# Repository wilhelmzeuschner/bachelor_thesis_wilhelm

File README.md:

# Bachelor Thesis Wilhelm Zeuschner
This repo contains select files of my bachelor thesis

More details can be found on my website where I wrote an article about my thesis.

www.wizeus.de/lmm-ba

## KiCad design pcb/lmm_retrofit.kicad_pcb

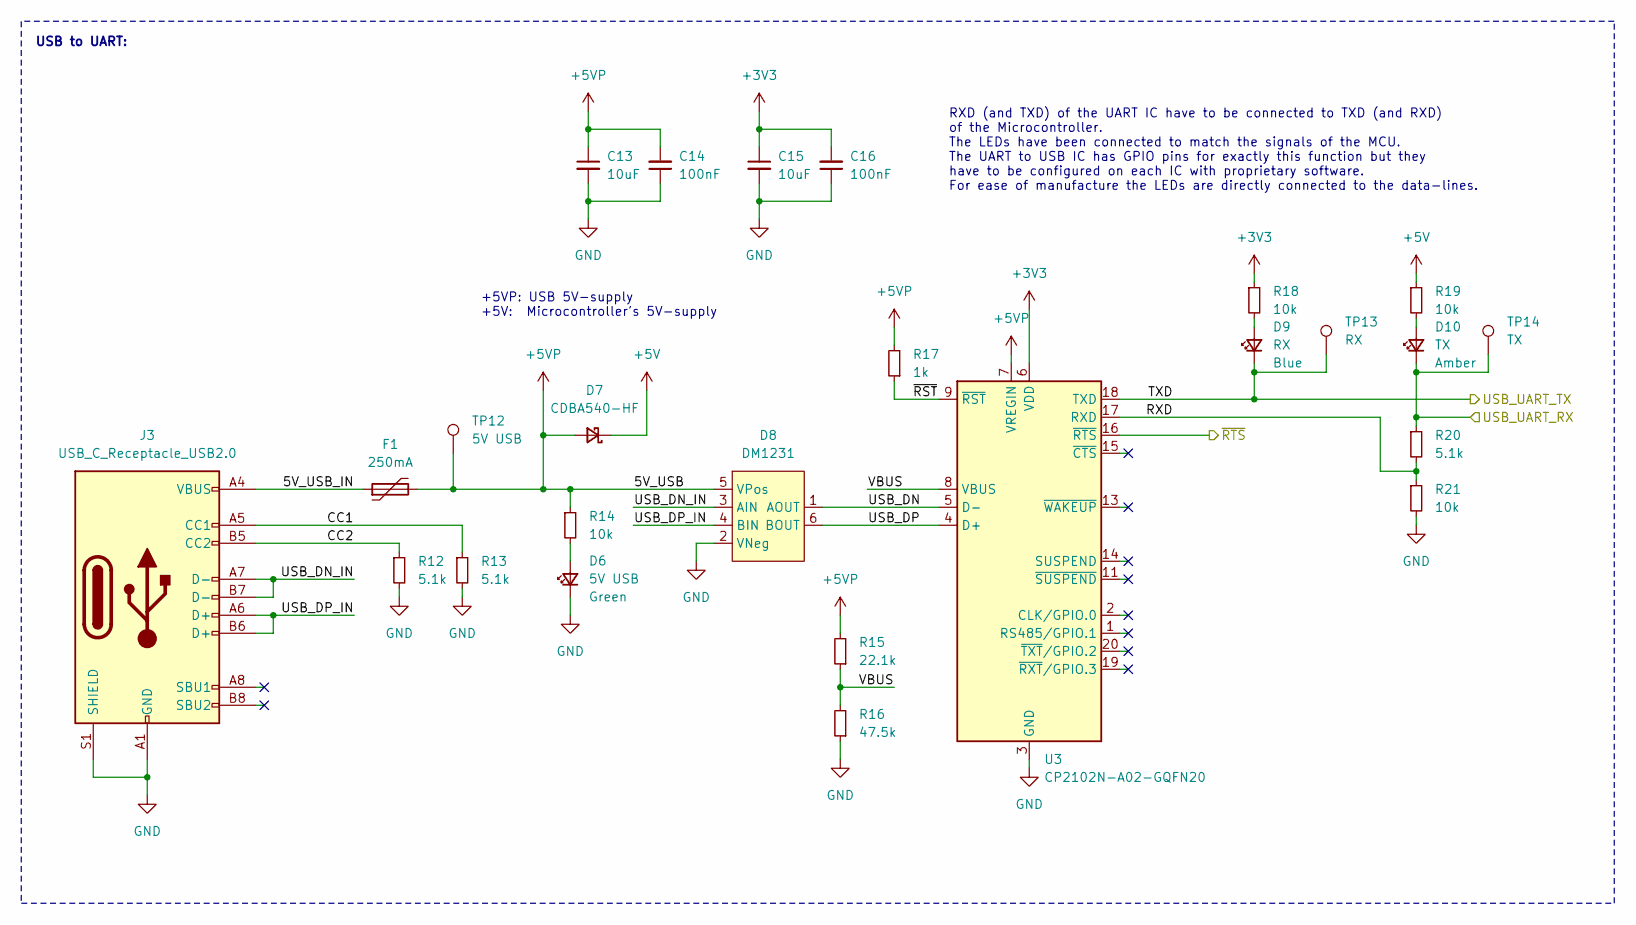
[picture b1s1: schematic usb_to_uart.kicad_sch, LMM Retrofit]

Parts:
C13, C15: 10uF; C_0805_2012Metric; MPN TMK212BBJ106MGHT; Digi-Key Part Number 587-6440-1-ND
C14, C16: 100nF; C_0805_2012Metric; MPN UMK212B7104KGHT; Digi-Key Part Number 587-3508-1-ND
D6: 5V USB; LED_0805_2012Metric_Silkscreen_Text; MPN 150080GS75000; Digi-Key Part Number 732-4983-1-ND
D7: CDBA540-HF; D_SMA; MPN CDBA540-HF; Digi-Key Part Number 641-1707-1-ND
D8: DM1231; SOT-23-6; MPN DM1231-02SO-7; Digi-Key Part Number DM1231-02SO-7DICT-ND
D9: RX; LED_0805_2012Metric_Silkscreen_Text; MPN 150080BS75000; Digi-Key Part Number 732-4982-1-ND
D10: TX; LED_0805_2012Metric_Silkscreen_Text; MPN 150080AS75000; Digi-Key Part Number 732-150080AS75000CT-ND
F1: 250mA; Fuse_1206_3216Metric; MPN 0ZCJ0025AF2E; Digi-Key Part Number 507-1799-1-ND
J3: USB_C_Receptacle_USB2.0; USB_C_Receptacle_GCT_USB4105-GF-A; MPN USB4105-GF-A; Digi-Key Part Number 2073-USB4105-GF-ACT-ND
R12, R13, R20: 5.1k; R_0805_2012Metric; MPN CRG0805F5K1; Digi-Key Part Number A126379CT-ND
R14, R18, R19, R21: 10k; R_0805_2012Metric; MPN CRGCQ0805J10K; Digi-Key Part Number A130140CT-ND
R15: 22.1k; R_0805_2012Metric; MPN CR0805-FX-2212ELF; Digi-Key Part Number CR0805-FX-2212ELFCT-ND
R16: 47.5k; R_0805_2012Metric; MPN CR0805-FX-4752ELF; Digi-Key Part Number 118-CR0805-FX-4752ELFCT-ND
R17: 1k; R_0805_2012Metric; MPN CRGCQ0805F1K0; Digi-Key Part Number A129749CT-ND
TP12: 5V USB; TestPoint_Pad_D1.0mm_Text_Silkscreen
TP13: RX; TestPoint_Pad_D1.0mm_Text_Silkscreen
TP14: TX; TestPoint_Pad_D1.0mm_Text_Silkscreen
U3: CP2102N-A02-GQFN20; SiliconLabs_QFN-20-1EP_3x3mm_P0.5mm_EP1.8x1.8mm_Center_Via; MPN CP2102N-A02-GQFN20; Digi-Key Part Number 336-5885-ND

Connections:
+3V3: C15.1, C16.2, R18.1, U3.6 (VDD)
+5V: D7.1 (K), R19.1; also elsewhere on the board
+5VP: C13.1, C14.2, D7.2 (A), D8.5 (VPos), F1.2, R14.1, R15.2, R17.2, TP12.1, U3.7 (VREGIN)
/Microcontroller/D0/UART_RX: D9.1 (K), TP13.1, U3.18 (TXD); also elsewhere on the board
/Microcontroller/D1/UART_TX: D10.1 (K), R20.1, TP14.1; also elsewhere on the board
/Microcontroller/~DTR: U3.16 (~RTS); also elsewhere on the board
/USB to UART/5V_USB_IN: F1.1, J3.A4 (VBUS), J3.A9 (VBUS), J3.B4 (VBUS), J3.B9 (VBUS)
/USB to UART/CC1: J3.A5 (CC1), R13.1
/USB to UART/CC2: J3.B5 (CC2), R12.1
/USB to UART/RXD: R20.2, R21.1, U3.17 (RXD)
/USB to UART/USB_DN: D8.1 (AOUT), U3.5 (D-)
/USB to UART/USB_DN_IN: D8.3 (AIN), J3.A7 (D-), J3.B7 (D-)
/USB to UART/USB_DP: D8.6 (BOUT), U3.4 (D+)
/USB to UART/USB_DP_IN: D8.4 (BIN), J3.A6 (D+), J3.B6 (D+)
/USB to UART/VBUS: R15.1, R16.2, U3.8 (VBUS)
/USB to UART/~RST: R17.1, U3.9 (~RST)
unnamed: D6.2 (A), R14.2
unnamed: D9.2 (A), R18.2
unnamed: D10.2 (A), R19.2

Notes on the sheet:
+5VP: USB 5V-supply +5V: Microcontroller's 5V-supply
USB to UART:
RXD (and TXD) of the UART IC have to be connected to TXD (and RXD) of the Microcontroller. The LEDs have been connected to match the signals of the MCU. The UART to USB IC has GPIO pins for exactly this function but they have to be configured on each IC with proprietary software. For ease of manufa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

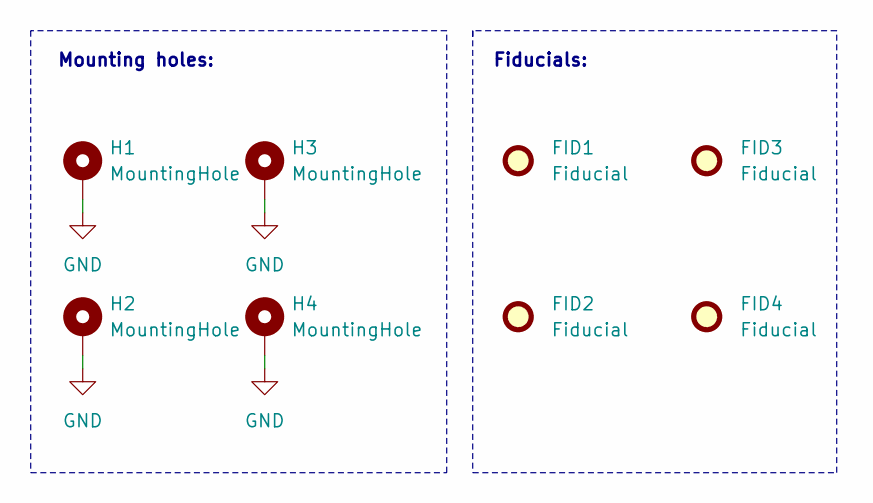
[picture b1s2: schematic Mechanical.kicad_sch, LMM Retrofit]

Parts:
FID1, FID2, FID3, FID4: Fiducial; Fiducial_0.5mm_Mask1mm
H1, H2, H3, H4: MountingHole; MountingHole_3.2mm_M3_Pad_Via

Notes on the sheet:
Fiducials:
Mounting holes:

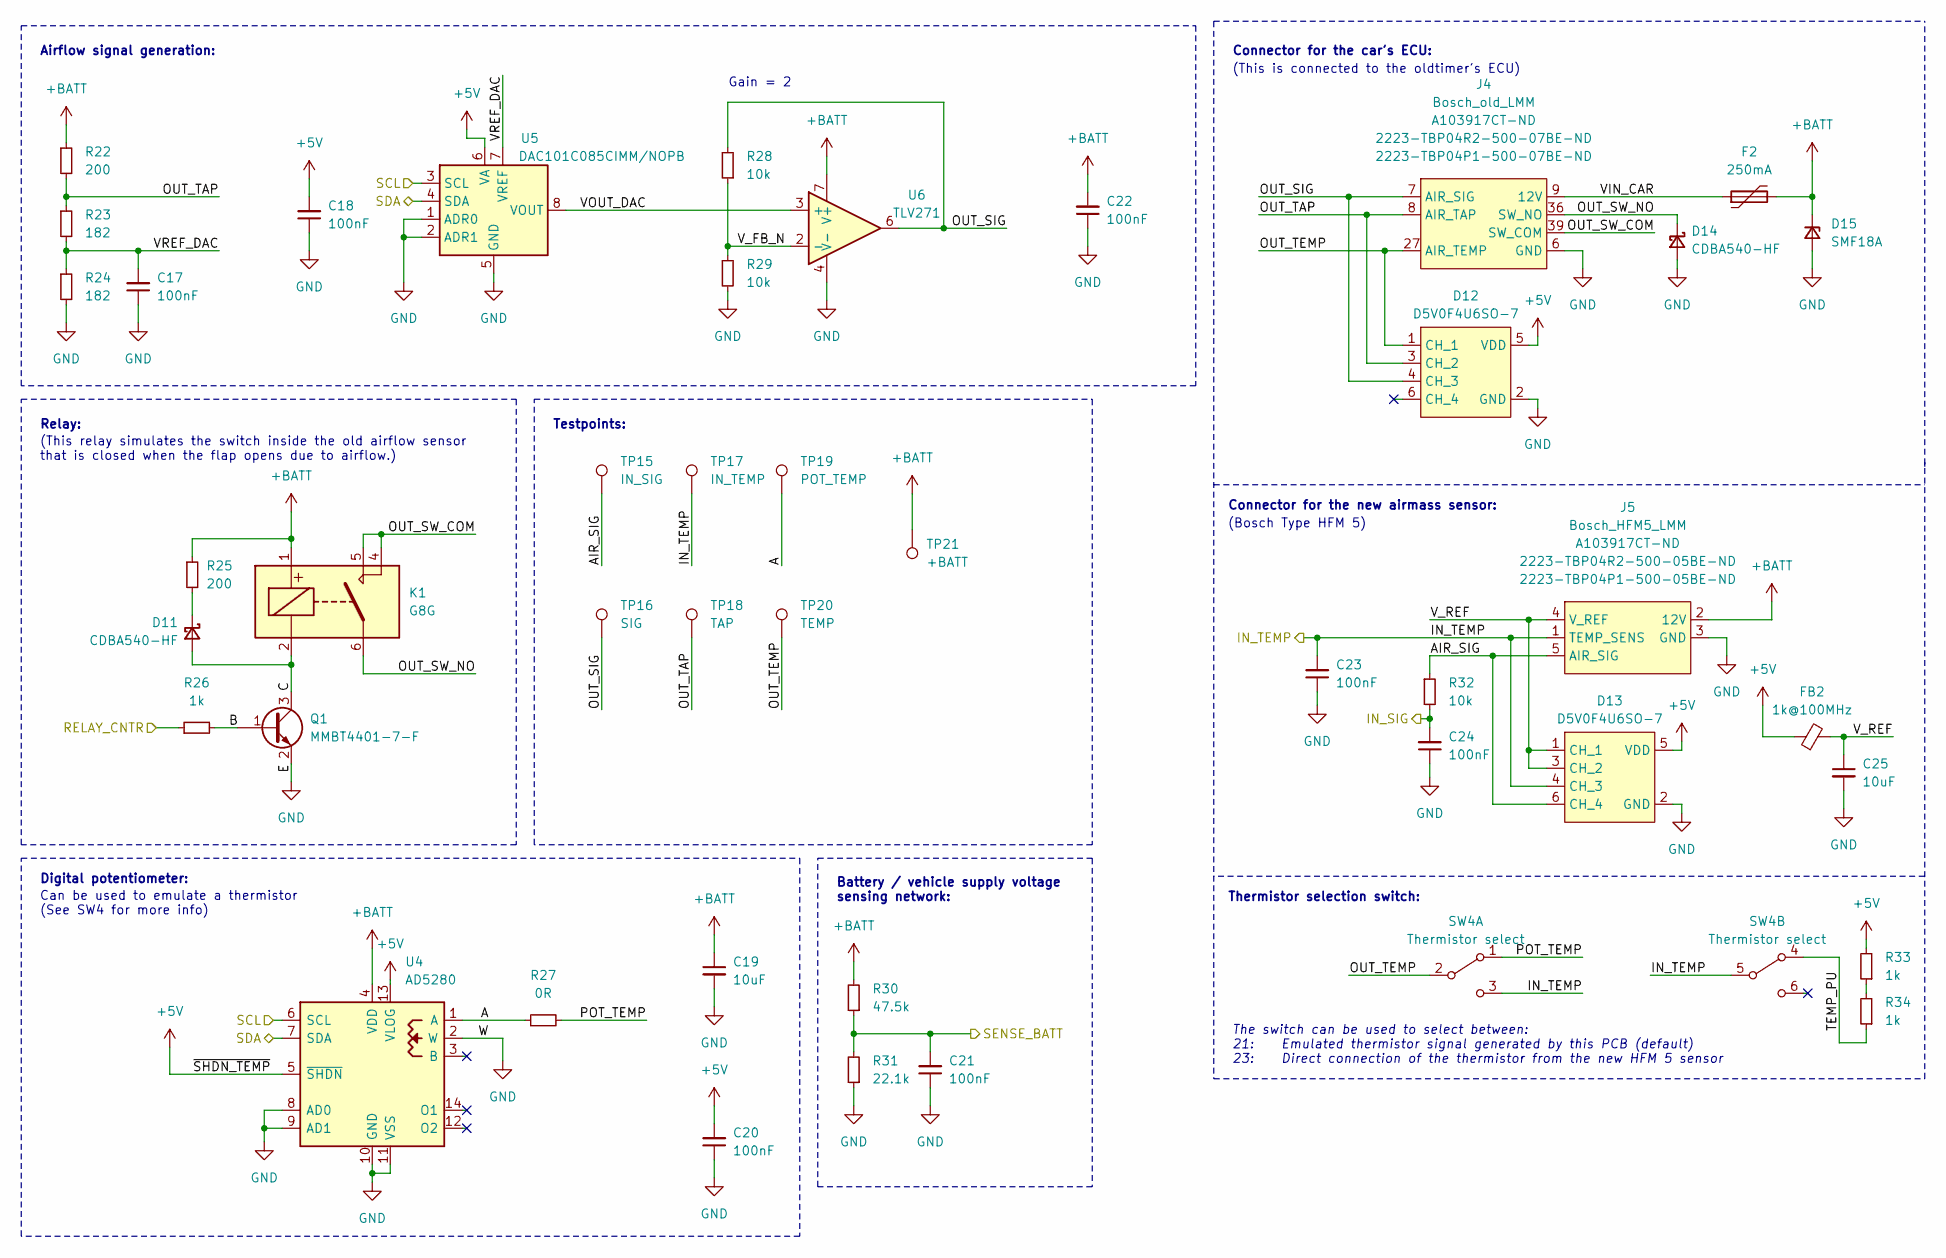
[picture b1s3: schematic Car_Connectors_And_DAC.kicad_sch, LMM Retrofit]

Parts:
C17, C18, C20, C21, C22, C23, C24: 100nF; C_0805_2012Metric; MPN UMK212B7104KGHT; Digi-Key Part Number 587-3508-1-ND
C19, C25: 10uF; C_0805_2012Metric; MPN TMK212BBJ106MGHT; Digi-Key Part Number 587-6440-1-ND
D11, D14: CDBA540-HF; D_SMA; MPN CDBA540-HF; Digi-Key Part Number 641-1707-1-ND
D12, D13: D5V0F4U6SO-7; SOT-23-6; MPN D5V0F4U6SO-7; Digi-Key Part Number D5V0F4U6SO-7DICT-ND
D15: SMF18A; D_SOD-123F; MPN SMF18A; Digi-Key Part Number F5820CT-ND
F2: 250mA; Fuse_1206_3216Metric; MPN 0ZCJ0025AF2E; Digi-Key Part Number 507-1799-1-ND
FB2: 1k@100MHz; L_0805_2012Metric; MPN ACML-0805-102-T; Digi-Key Part Number 535-ACML-0805-102-TCT-ND
J4: Bosch_old_LMM; Bosch_L_Jetronic_7-Pin_Male_Blade_Conn; MPN 0 280 203 002
J5: Bosch_HFM5_LMM; Bosch_Airmass_Senosor_5-Pin_Male_Blade_Connector; MPN 0 280 217 531
K1: G8G; G8G__SPST; MPN G8G-1A7R DC12 BY OMR1; Digi-Key Part Number 39-G8G-1A7RDC12BYOMR1-ND
Q1: MMBT4401-7-F; SOT-23; MPN MMBT4401-HF; Digi-Key Part Number 641-MMBT4401-HFCT-ND
R22, R25: 200; R_0805_2012Metric; MPN ESR10EZPF2000; Digi-Key Part Number RHM200AECT-ND
R23, R24: 182; R_0805_2012Metric; MPN CRCW0805182RFKEA; Digi-Key Part Number 541-182CCT-ND
R26, R33, R34: 1k; R_0805_2012Metric; MPN CRGCQ0805F1K0; Digi-Key Part Number A129749CT-ND
R27: 0R; R_0805_2012Metric; MPN AC0805JR-070RL; Digi-Key Part Number YAG3755CT-ND
R28, R29, R32: 10k; R_0805_2012Metric; MPN CRGCQ0805J10K; Digi-Key Part Number A130140CT-ND
R30: 47.5k; R_0805_2012Metric; MPN CR0805-FX-4752ELF; Digi-Key Part Number 118-CR0805-FX-4752ELFCT-ND
R31: 22.1k; R_0805_2012Metric; MPN CR0805-FX-2212ELF; Digi-Key Part Number CR0805-FX-2212ELFCT-ND
SW4: Thermistor select; JS202011SCQN; MPN JS202011SCQN; Digi-Key Part Number 401-2002-1-ND
TP15: IN_SIG; TestPoint_Pad_D1.0mm_Text_Silkscreen
TP16: SIG; TestPoint_Pad_D1.0mm_Text_Silkscreen
TP17: IN_TEMP; TestPoint_Pad_D1.0mm_Text_Silkscreen
TP18: TAP; TestPoint_Pad_D1.0mm_Text_Silkscreen
TP19: POT_TEMP; TestPoint_Pad_D1.0mm_Text_Silkscreen
TP20: TEMP; TestPoint_Pad_D1.0mm_Text_Silkscreen
TP21: +BATT; TestPoint_Pad_D1.0mm_Text_Silkscreen
U4: AD5280; TSSOP-14_4.4x5mm_P0.65mm; MPN AD5280BRUZ50; Digi-Key Part Number AD5280BRUZ50-ND
U5: DAC101C085CIMM/NOPB; VSSOP-8_3.0x3.0mm_P0.65mm; MPN DAC101C085CIMM/NOPB; Digi-Key Part Number DAC101C085CIMM/NOPBCT-ND
U6: TLV271; SOIC-8_3.9x4.9mm_P1.27mm; MPN TLV271QDRQ1; Digi-Key Part Number 296-38281-1-ND

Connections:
+5V: C18.2, C20.2, D12.5 (VDD), D13.5 (VDD), FB2.1, R33.2, U4.5 (~SHDN), U4.13 (VLOG), U5.6 (VA); also elsewhere on the board
+BATT: C19.1, C22.2, D15.1 (K), F2.2, J5.2 (12V), K1.1, R22.1, R25.1, R30.2, TP21.1, U4.4 (VDD), U6.7 (V+); also elsewhere on the board
/Car_Connectors_And_DAC/A: R27.1, TP19.1, U4.1 (A)
/Car_Connectors_And_DAC/AIR_SIG: D13.6 (CH_4), J5.5 (AIR_SIG), R32.1, TP15.1
/Car_Connectors_And_DAC/B: Q1.1 (B), R26.2
/Car_Connectors_And_DAC/C: D11.2 (A), K1.2, Q1.3 (C)
/Car_Connectors_And_DAC/IN_TEMP: C23.2, D13.4 (CH_3), J5.1 (TEMP_SENS), SW4.3 (C), SW4.5 (B), TP17.1; also elsewhere on the board
/Car_Connectors_And_DAC/OUT_SIG: D12.4 (CH_3), J4.7 (AIR_SIG), R28.2, TP16.1, U6.6
/Car_Connectors_And_DAC/OUT_SW_COM: J4.39 (SW_COM), K1.4, K1.5
/Car_Connectors_And_DAC/OUT_SW_NO: D14.1 (K), J4.36 (SW_NO), K1.6
/Car_Connectors_And_DAC/OUT_TAP: D12.3 (CH_2), J4.8 (AIR_TAP), R22.2, R23.1, TP18.1
/Car_Connectors_And_DAC/OUT_TEMP: D12.1 (CH_1), J4.27 (AIR_TEMP), SW4.2 (B), TP20.1
/Car_Connectors_And_DAC/POT_TEMP: R27.2, SW4.1 (A)
/Car_Connectors_And_DAC/TEMP_PU: R34.1, SW4.4 (A)
/Car_Connectors_And_DAC/VIN_CAR: F2.1, J4.9 (12V)
/Car_Connectors_And_DAC/VOUT_DAC: U5.8 (VOUT), U6.3 (+)
/Car_Connectors_And_DAC/VREF_DAC: C17.2, R23.2, R24.1, U5.7 (VREF)
/Car_Connectors_And_DAC/V_FB_N: R28.1, R29.1, U6.2 (-)
/Car_Connectors_And_DAC/V_REF: C25.1, D13.1 (CH_1), D13.3 (CH_2), FB2.2, J5.4 (V_REF)
/Microcontroller/A0/SIG: C24.2, R32.2; also elsewhere on the board
/Microcontroller/A4/SDA: U4.7 (SDA), U5.4 (SDA); also elsewhere on the board
/Microcontroller/A5/SCL: U4.6 (SCL), U5.3 (SCL); also elsewhere on the board
/Microcontroller/A6/BATT: C21.2, R30.1, R31.2; also elsewhere on the board
/Microcontroller/D4/RELAY: R26.1; also elsewhere on the board
unnamed: D11.1 (K), R25.2
unnamed: R33.1, R34.2

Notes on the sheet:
Testpoints:
Battery / vehicle supply voltage sensing network:
Connector for the car's ECU:
The switch can be used to select between: 21: Emulated thermistor signal generated by this PCB (default) 23: Direct connection of the thermistor from the new HFM 5 sensor
Digital potentiometer:
Thermistor selection switch:
(Bosch Type HFM 5)
Relay:
Airflow signal generation:
Connector for the new airmass sensor:
Gain = 2
(This relay simulates the switch inside the old airflow sensor that is closed when the flap opens due to airflow.)
(This is connected to the oldtimer's ECU)
Can be used to emulate a thermistor (See SW4 for more info)

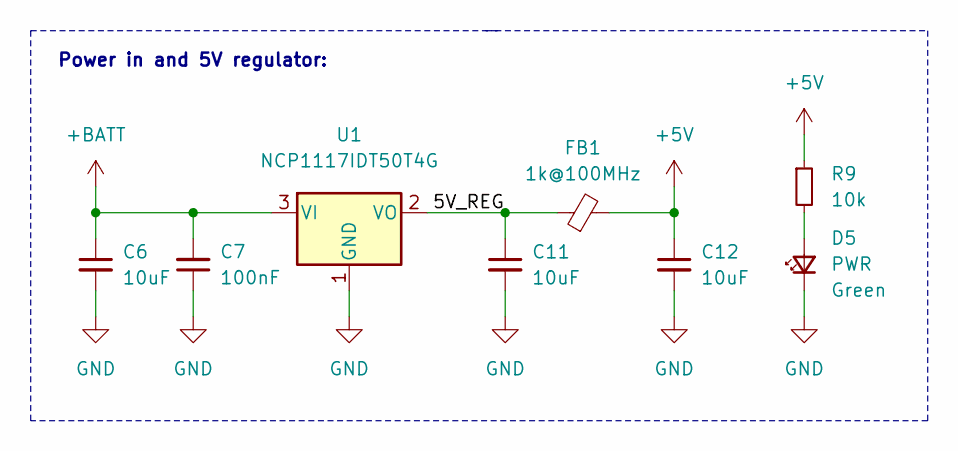
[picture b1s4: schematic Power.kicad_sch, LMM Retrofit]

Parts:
C6, C11, C12: 10uF; C_0805_2012Metric; MPN TMK212BBJ106MGHT; Digi-Key Part Number 587-6440-1-ND
C7: 100nF; C_0805_2012Metric; MPN UMK212B7104KGHT; Digi-Key Part Number 587-3508-1-ND
D5: PWR; LED_0805_2012Metric_Silkscreen_Text; MPN 150080GS75000; Digi-Key Part Number 732-4983-1-ND
FB1: 1k@100MHz; L_0805_2012Metric; MPN ACML-0805-102-T; Digi-Key Part Number 535-ACML-0805-102-TCT-ND
R9: 10k; R_0805_2012Metric; MPN CRGCQ0805J10K; Digi-Key Part Number A130140CT-ND
U1: NCP1117IDT50T4G; TO-252-2; MPN NCP1117IDT50T4G; Digi-Key Part Number 488-NCP1117IDT50T4GCT-ND

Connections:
+5V: C12.1, FB1.2, R9.1; also elsewhere on the board
+BATT: C6.1, C7.2, U1.3 (VI); also elsewhere on the board
/Power/5V_REG: C11.1, FB1.1, U1.2 (VO)
unnamed: D5.2 (A), R9.2

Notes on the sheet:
Power in and 5V regulator:

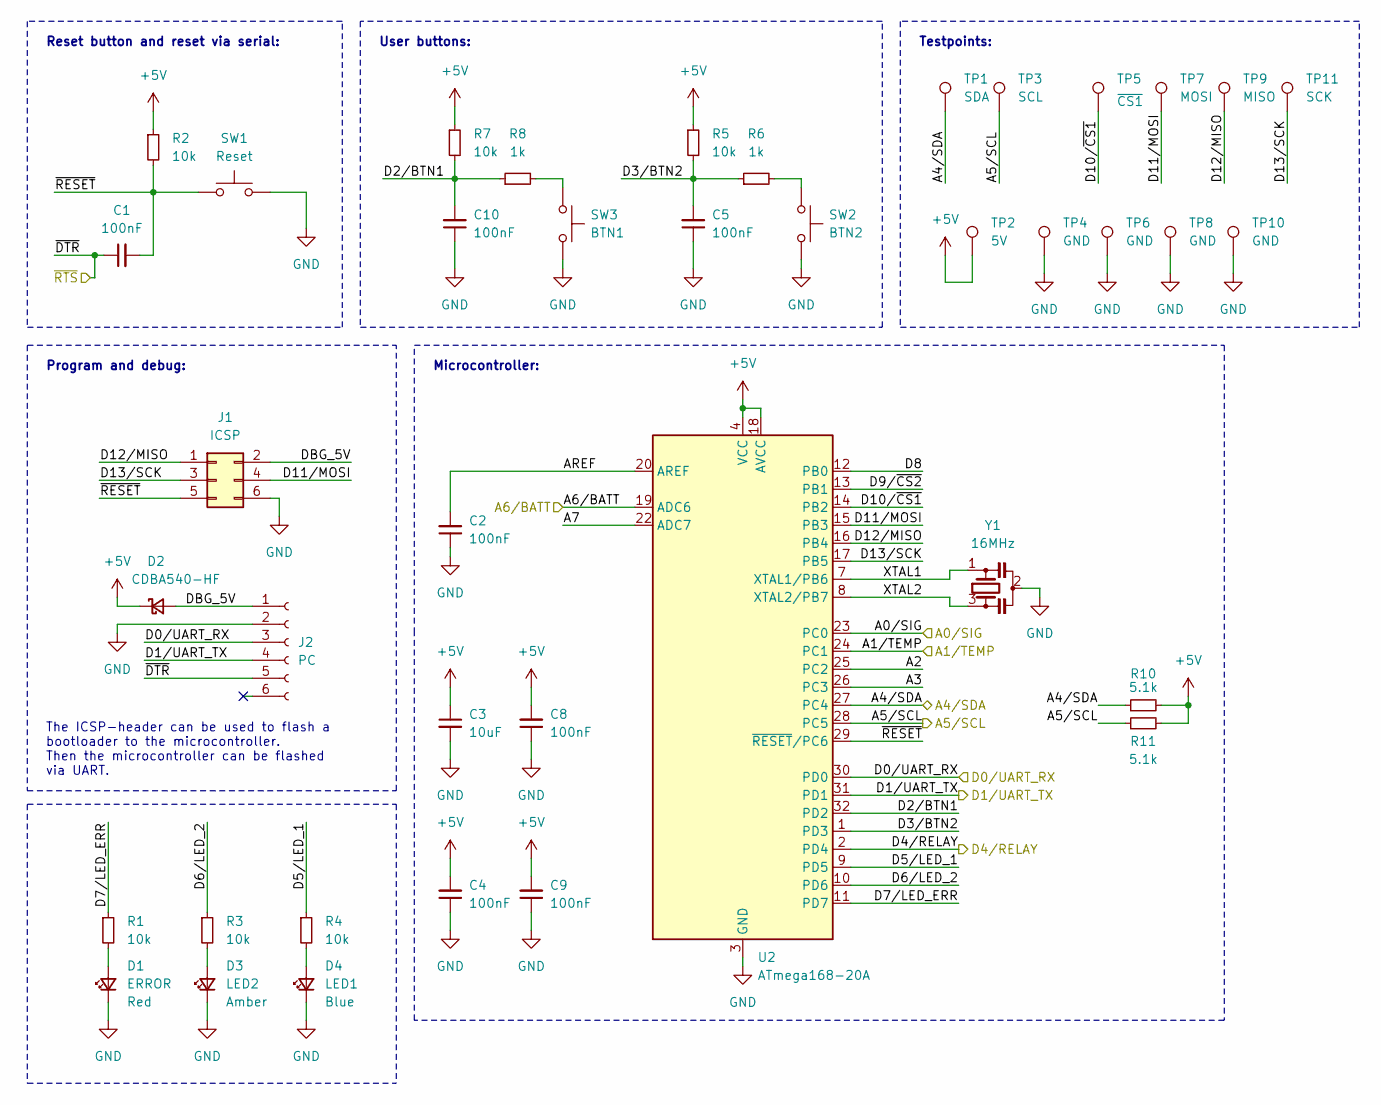
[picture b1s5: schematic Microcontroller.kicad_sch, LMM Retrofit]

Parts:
C1, C2, C4, C5, C8, C9, C10: 100nF; C_0805_2012Metric; MPN UMK212B7104KGHT; Digi-Key Part Number 587-3508-1-ND
C3: 10uF; C_0805_2012Metric; MPN TMK212BBJ106MGHT; Digi-Key Part Number 587-6440-1-ND
D1: ERROR; LED_0805_2012Metric_Silkscreen_Text; MPN 150080RS75000; Digi-Key Part Number 732-4984-1-ND
D2: CDBA540-HF; D_SMA; MPN CDBA540-HF; Digi-Key Part Number 641-1707-1-ND
D3: LED2; LED_0805_2012Metric_Silkscreen_Text; MPN 150080AS75000; Digi-Key Part Number 732-150080AS75000CT-ND
D4: LED1; LED_0805_2012Metric_Silkscreen_Text; MPN 150080BS75000; Digi-Key Part Number 732-4982-1-ND
J1: ICSP; PinHeader_2x03_P2.54mm_Horizontal; MPN PH2RA-06-UA; Digi-Key Part Number 2057-PH2RA-06-UA-ND
J2: PC; PinSocket_1x06_P2.54mm_Horizontal; MPN FR20206HBNN; Digi-Key Part Number 1849-FR20206HBNN-ND
R1, R2, R3, R4, R5, R7: 10k; R_0805_2012Metric; MPN CRGCQ0805J10K; Digi-Key Part Number A130140CT-ND
R6, R8: 1k; R_0805_2012Metric; MPN CRGCQ0805F1K0; Digi-Key Part Number A129749CT-ND
R10, R11: 5.1k; R_0805_2012Metric; MPN CRG0805F5K1; Digi-Key Part Number A126379CT-ND
SW1: Reset; PTS815_SMT_Push_Button; MPN PTS815 SJK 250 SMTR LFS; Digi-Key Part Number CKN12216-1-ND
SW2: BTN2; SW_PUSH_6mm_H9.5mm; MPN TS03-66-95-BK-260-LCR-D-67; Digi-Key Part Number 2223-TS03-66-95-BK-260-LCR-D-67-ND
SW3: BTN1; SW_PUSH_6mm_H9.5mm; MPN TS03-66-95-BK-260-LCR-D-67; Digi-Key Part Number 2223-TS03-66-95-BK-260-LCR-D-67-ND
TP1: SDA; TestPoint_Pad_D1.0mm_Text_Silkscreen
TP2: 5V; TestPoint_Pad_D1.0mm_Text_Silkscreen
TP3: SCL; TestPoint_Pad_D1.0mm_Text_Silkscreen
TP4, TP6, TP8, TP10: GND; TestPoint_Pad_D1.0mm_Text_Silkscreen
TP5: ~{CS1}; TestPoint_Pad_D1.0mm_Text_Silkscreen
TP7: MOSI; TestPoint_Pad_D1.0mm_Text_Silkscreen
TP9: MISO; TestPoint_Pad_D1.0mm_Text_Silkscreen
TP11: SCK; TestPoint_Pad_D1.0mm_Text_Silkscreen
U2: ATmega168-20A; TQFP-32_7x7mm_P0.8mm; MPN ATMEGA168-20AU; Digi-Key Part Number ATMEGA168-20AU-ND
Y1: 16MHz; Resonator_SMD_Murata_CSTxExxV-3Pin_3.0x1.1mm; MPN CSTNE16M0V530000R0; Digi-Key Part Number 490-17948-1-ND

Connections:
+5V: C3.1, C4.2, C8.2, C9.2, D2.1 (K), R2.1, R5.1, R7.1, R10.2, R11.2, TP2.1, U2.4 (VCC), U2.6 (VCC), U2.18 (AVCC); also elsewhere on the board
/Car_Connectors_And_DAC/IN_TEMP: U2.24 (PC1); also elsewhere on the board
/Microcontroller/A0/SIG: U2.23 (PC0); also elsewhere on the board
/Microcontroller/A2: U2.25 (PC2)
/Microcontroller/A3: U2.26 (PC3)
/Microcontroller/A4/SDA: R10.1, TP1.1, U2.27 (PC4); also elsewhere on the board
/Microcontroller/A5/SCL: R11.1, TP3.1, U2.28 (PC5); also elsewhere on the board
/Microcontroller/A6/BATT: U2.19 (ADC6); also elsewhere on the board
/Microcontroller/A7: U2.22 (ADC7)
/Microcontroller/AREF: C2.2, U2.20 (AREF)
/Microcontroller/D0/UART_RX: J2.3, U2.30 (PD0); also elsewhere on the board
/Microcontroller/D1/UART_TX: J2.4, U2.31 (PD1); also elsewhere on the board
/Microcontroller/D2/BTN1: C10.2, R7.2, R8.1, U2.32 (PD2)
/Microcontroller/D3/BTN2: C5.2, R5.2, R6.1, U2.1 (PD3)
/Microcontroller/D4/RELAY: U2.2 (PD4); also elsewhere on the board
/Microcontroller/D5/LED_1: R4.1, U2.9 (PD5)
/Microcontroller/D6/LED_2: R3.1, U2.10 (PD6)
/Microcontroller/D7/LED_ERR: R1.1, U2.11 (PD7)
/Microcontroller/D8: U2.12 (PB0)
/Microcontroller/D9/~CS2: U2.13 (PB1)
/Microcontroller/D10/~CS1: TP5.1, U2.14 (PB2)
/Microcontroller/D11/MOSI: J1.4, TP7.1, U2.15 (PB3)
/Microcontroller/D12/MISO: J1.1, TP9.1, U2.16 (PB4)
/Microcontroller/D13/SCK: J1.3, TP11.1, U2.17 (PB5)
/Microcontroller/DBG_5V: D2.2 (A), J1.2, J2.1
/Microcontroller/XTAL1: U2.7 (XTAL1/PB6), Y1.1
/Microcontroller/XTAL2: U2.8 (XTAL2/PB7), Y1.3
/Microcontroller/~DTR: C1.1, J2.5; also elsewhere on the board
/Microcontroller/~RESET: C1.2, J1.5, R2.2, SW1.1, SW1.2, U2.29 (~RESET/PC6)
unnamed: D1.2 (A), R1.2
unnamed: D3.2 (A), R3.2
unnamed: D4.2 (A), R4.2
unnamed: R6.2, SW2.1
unnamed: R8.2, SW3.1

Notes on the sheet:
Reset button and reset via serial:
User buttons:
Program and debug:
Testpoints:
The ICSP-header can be used to flash a bootloader to the microcontroller. Then the microcontroller can be flashed via UART.
Microcontroller:

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
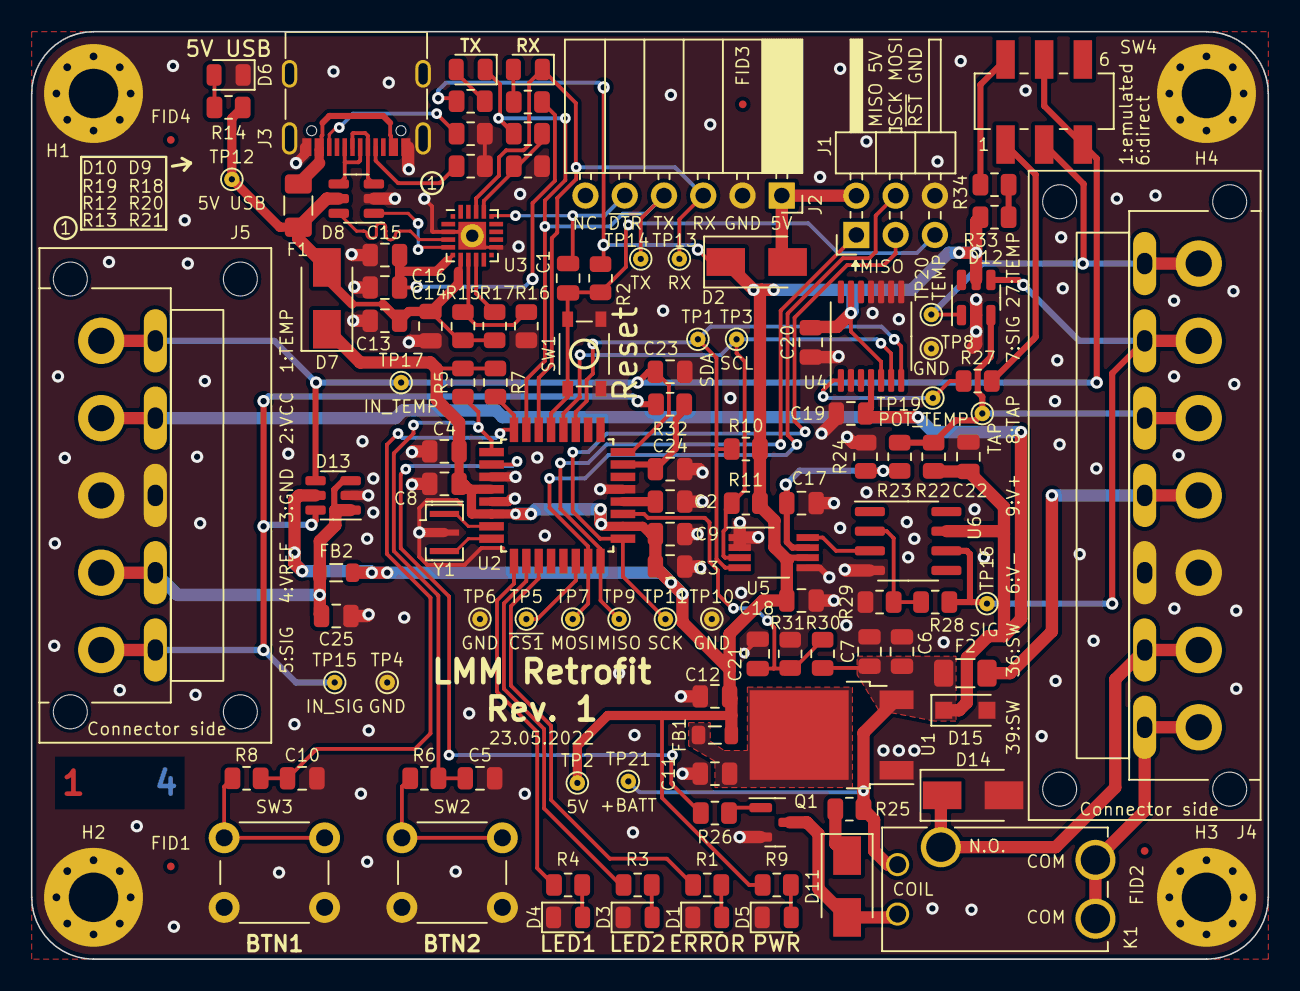
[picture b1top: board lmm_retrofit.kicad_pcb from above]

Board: 4 copper layers, 80.0 x 60.0 mm, 125 parts (0 on the bottom side), 66 nets.

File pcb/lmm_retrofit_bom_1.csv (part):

Component,Description,Part,References,Value,Footprint,Quantity Per PCB,Datasheet,Digi-Key Part Number,MPN,Color,DNF,Info
1,"Unpolarized capacitor, small symbol",C_Small,C1 C2 C4 C5 C7 C8 C9 C10 C14 C16 C17 C18 C20 C21 C22 C23 C24,100nF,C_0805_2012Metric,17,https://www.yuden.co.jp/productdata/catalog/mlcc_all_hq_e.pdf,587-3508-1-ND,UMK212B7104KGHT,,,
2,"Unpolarized capacitor, small symbol",C_Small,C3 C6 C11 C12 C13 C15 C19 C25,10uF,C_0805_2012Metric,8,https://ds.yuden.co.jp/TYCOMPAS/ut/detail?pn=MCAST21GBB5106M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,587-6440-1-ND,TMK212BBJ106MGHT,,,
3,"Light emitting diode, small symbol",LED_Small,D6,5V USB,LED_0805_2012Metric_Silkscreen_Text,1,https://www.we-online.com/katalog/datasheet/150080GS75000.pdf,732-4983-1-ND,150080GS75000,Green,,
4,"Schottky diode, small symbol",D_Schottky_Small,D2 D7 D11 D14,CDBA540-HF,D_SMA,4,https://media.digikey.com/pdf/Data%20Sheets/Comchip%20PDFs/C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,641-1707-1-ND,CDBA540-HF,,,
5,12V Clamp 3A (8/20µs) Ipp Tvs Diode Surface Mount SOT-26,D5V0F4U6SO-7,D12 D13,D5V0F4U6SO-7,SOT-23-6,2,https://www.diodes.com/assets/Datasheets/D5V0F4U6SO.pdf,D5V0F4U6SO-7DICT-ND,D5V0F4U6SO-7,,,
6,14V Clamp 7A (8/20µs) Ipp Tvs Diode Surface Mount SOT-26,DM1231,D8,DM1231,SOT-23-6,1,https://media.digikey.com/pdf/Data%20Sheets/Diodes%20PDFs/DM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,DM1231-02SO-7DICT-ND,DM1231-02SO-7,,,
7,"Light emitting diode, small symbol",LED_Small,D1,ERROR,LED_0805_2012Metric_Silkscreen_Text,1,https://www.we-online.com/katalog/datasheet/150080RS75000.pdf,732-4984-1-ND,150080RS75000,Red,,
8,"Light emitting diode, small symbol",LED_Small,D4,LED1,LED_0805_2012Metric_Silkscreen_Text,1,https://www.we-online.com/katalog/datasheet/150080BS75000.pdf,732-4982-1-ND,150080BS75000,Blue,,
9,"Light emitting diode, small symbol",LED_Small,D3,LED2,LED_0805_2012Metric_Silkscreen_Text,1,https://www.mouser.de/datasheet/2/445/150080AS75000-1879102.pdf,732-150080AS75000CT-ND,150080AS75000,Amber,,
10,"Light emitting diode, small symbol",LED_Small,D5,PWR,LED_0805_2012Metric_Silkscreen_Text,1,https://www.we-online.com/katalog/datasheet/150080GS75000.pdf,732-4983-1-ND,150080GS75000,Green,,
11,"Light emitting diode, small symbol",LED_Small,D9,RX,LED_0805_2012Metric_Silkscreen_Text,1,https://www.we-online.com/katalog/datasheet/150080BS75000.pdf,732-4982-1-ND,150080BS75000,Blue,,
12,"Zener diode, small symbol",D_Zener_Small,D15,SMF18A,D_SOD-123F,1,https://www.littelfuse.com/~/media/electronics/datasheets/tv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,F5820CT-ND,SMF18A,,,
13,"Light emitting diode, small symbol",LED_Small,D10,TX,LED_0805_2012Metric_Silkscreen_Text,1,https://www.mouser.de/datasheet/2/445/150080AS75000-1879102.pdf,732-150080AS75000CT-ND,150080AS75000,Amber,,
14,"Resettable fuse, polymeric positive temperature coefficient",Polyfuse,F1 F2,250mA,Fuse_1206_3216Metric,2,https://www.belfuse.com/resources/datasheets/circuitprotecti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,507-1799-1-ND,0ZCJ0025AF2E,,,
15,"Ferrite bead, small symbol",FerriteBead_Small,FB1 FB2,1k@100MHz,L_0805_2012Metric,2,https://abracon.com/Magnetics/new/ACML-0805.pdf,535-ACML-0805-102-TCT-ND,ACML-0805-102-T,,,
16,"Hot-film air-mass meter, Type HFM 5",Bosch_HFM5_LMM,J5,Bosch_HFM5_LMM,Bosch_Airmass_Senosor_5-Pin_Male_Blade_Connector,1,https://mux.hs-emden-leer.de/svn/micro-projects-lmm/30_datas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,,0 280 217 531,,Do not fit,
17,Airflow meter for L Jetronic ECUs; Luftmengenmesser für Oldtimer,Bosch_old_LMM,J4,Bosch_old_LMM,Bosch_L_Jetronic_7-Pin_Male_Blade_Conn,1,https://mux.hs-emden-leer.de/svn/micro-projects-lmm/30_datas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,,0 280 203 002,,Do not fit,
18,"Generic connector, double row, 02x03, odd/even pin numbering scheme (row 1 odd numbers, row 2 even numbers), script generated (kicad-library-utils/schlib/autogen/connector/)",Conn_02x03_Odd_Even,J1,ICSP,PinHeader_2x03_P2.54mm_Horizontal,1,https://app.adam-tech.com/products/download/data_sheet/20050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,2057-PH2RA-06-UA-ND,PH2RA-06-UA,,,
19,"Generic connector, single row, 01x06, script generated (kicad-library-utils/schlib/autogen/connector/)",Conn_01x06_Female,J2,PC,PinSocket_1x06_P2.54mm_Horizontal,1,https://media.metz-connect.com/files/171/Data_sheet_FR202XXHBNN.PDF,1849-FR20206HBNN-ND,FR20206HBNN,,,
20,USB 2.0-only Type-C Receptacle connector,USB_C_Receptacle_USB2.0,J3,USB_C_Receptacle_USB2.0,USB_C_Receptacle_GCT_USB4105-GF-A,1,https://gct.co/files/drawings/usb4105.pdf,2073-USB4105-GF-ACT-ND,USB4105-GF-A,,,
21,"AUTO MOTIVE PCB RELAY, DC 12V",G8G,K1,G8G,G8G__SPST,1,https://components.omron.com/us-en/datasheet_pdf/J263-E1.pdf,39-G8G-1A7RDC12BYOMR1-ND,G8G-1A7R DC12 BY OMR1,,,
22,"NPN transistor, base/emitter/collector",Q_NPN_BEC,Q1,MMBT4401-7-F,SOT-23,1,https://www.comchiptech.com/admin/files/product/QW-JTR91%20M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,641-MMBT4401-HFCT-ND,MMBT4401-HF,,,
23,"Resistor, small symbol",R_Small,R27,0R,R_0805_2012Metric,1,https://www.yageo.com/upload/media/product/productsearch/dat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,YAG3755CT-ND,AC0805JR-070RL,,,Populate with value >0R if voltage on A pin would be too high.
24,"Resistor, small symbol",R_Small,R23 R24,182,R_0805_2012Metric,2,https://www.vishay.com/docs/20035/dcrcwe3.pdf,541-182CCT-ND,CRCW0805182RFKEA,,,
25,"Resistor, small symbol",R_Small,R22 R25,200,R_0805_2012Metric,2,https://fscdn.rohm.com/en/products/databook/datasheet/passiv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,RHM200AECT-ND,ESR10EZPF2000,,,
26,"Resistor, small symbol",R_Small,R6 R8 R17 R26 R33 R34,1k,R_0805_2012Metric,6,https://www.te.com/commerce/DocumentDelivery/DDEController?A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,A129749CT-ND,CRGCQ0805F1K0,,,
27,"Resistor, small symbol",R_Small,R10 R11 R12 R13 R20,5.1k,R_0805_2012Metric,5,https://www.te.com/commerce/DocumentDelivery/DDEController?A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,A126379CT-ND,CRG0805F5K1,,,
28,"Resistor, small symbol",R_Small,R1 R2 R3 R4 R5 R7 R9 R14 R18 R19 R21 R28 R29 R32,10k,R_0805_2012Metric,14,https://www.te.com/commerce/DocumentDelivery/DDEController?A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,A130140CT-ND,CRGCQ0805J10K,,,
29,"Resistor, small symbol",R_Small,R15 R31,22.1k,R_0805_2012Metric,2,https://www.bourns.com/docs/product-datasheets/cr.pdf?sfvrsn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,CR0805-FX-2212ELFCT-ND,CR0805-FX-2212ELF,,,
30,"Resistor, small symbol",R_Small,R16 R30,47.5k,R_0805_2012Metric,2,https://www.bourns.com/docs/product-datasheets/cr.pdf?sfvrsn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,118-CR0805-FX-4752ELFCT-ND,CR0805-FX-4752ELF,,,
31,"Push button switch, generic, two pins",SW_Push,SW3,BTN1,SW_PUSH_6mm_H9.5mm,1,https://www.cuidevices.com/product/resource/ts03.pdf,2223-TS03-66-95-BK-260-LCR-D-67-ND,TS03-66-95-BK-260-LCR-D-67,,,
32,"Push button switch, generic, two pins",SW_Push,SW2,BTN2,SW_PUSH_6mm_H9.5mm,1,https://www.cuidevices.com/product/resource/ts03.pdf,2223-TS03-66-95-BK-260-LCR-D-67-ND,TS03-66-95-BK-260-LCR-D-67,,,
33,"Push button switch, four pins, both channels connected",CKN12216-1-ND,SW1,Reset,PTS815_SMT_Push_Button,1,https://www.ckswitches.com/media/2728/pts815.pdf,CKN12216-1-ND,PTS815 SJK 250 SMTR LFS,,,
34,"Switch, dual pole double throw, separate symbols",SW_DPDT_x2,SW4,Thermistor select,JS202011SCQN,1,https://www.ckswitches.com/media/1422/js.pdf,401-2002-1-ND,JS202011SCQN,,,
35,"Digital potentiometer, 256 position, single output, I2C interface",AD5280,U4,AD5280,TSSOP-14_4.4x5mm_P0.65mm,1,https://www.analog.com/media/en/technical-documentation/data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,AD5280BRUZ50-ND,AD5280BRUZ50,,,
36,"20MHz, 16kB Flash, 1kB SRAM, 512B EEPROM, TQFP-32",ATmega168-20A,U2,ATmega168-20A,TQFP-32_7x7mm_P0.8mm,1,http://ww1.microchip.com/downloads/en/DeviceDoc/Atmel-2545-8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,ATMEGA168-20AU-ND,ATMEGA168-20AU,,,
37,"USB to UART master bridge, QFN-20",CP2102N-Axx-xQFN20,U3,CP2102N-A02-GQFN20,SiliconLabs_QFN-20-1EP_3x3mm_P0.5mm_EP1.8x1.8mm_Center_Via,1,https://www.silabs.com/documents/public/data-sheets/cp2102n-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,336-5885-ND,CP2102N-A02-GQFN20,,,
38,10 Bit Digital to Analog Converter 1 8-VSSOP,DAC101C085CIMM{slash}NOPB,U5,DAC101C085CIMM/NOPB,VSSOP-8_3.0x3.0mm_P0.65mm,1,http://www.ti.com/lit/ds/symlink/dac101c081.pdf,DAC101C085CIMM/NOPBCT-ND,DAC101C085CIMM/NOPB,,,
39,"1A Low drop-out regulator, Fixed Output 5.0V, TO-252 (DPAK)",NCP1117-5.0_TO252,U1,NCP1117IDT50T4G,TO-252-2,1,https://www.onsemi.com/pdf/datasheet/ncp1117-d.pdf,488-NCP1117IDT50T4GCT-ND,NCP1117IDT50T4G,,,
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
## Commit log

2024-08-10 add files
2024-08-10 added pcb files
2024-08-10 3d design
